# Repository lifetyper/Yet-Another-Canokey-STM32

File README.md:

# Yet-Another-Canokey-STM32
使用USBA Connector替代PCB金手指形式的焊盘，降低在加工厂打样的PCB成本。原理图和官方[Canokey-STM32](https://github.com/canokeys/canokey-stm32)版本一致。

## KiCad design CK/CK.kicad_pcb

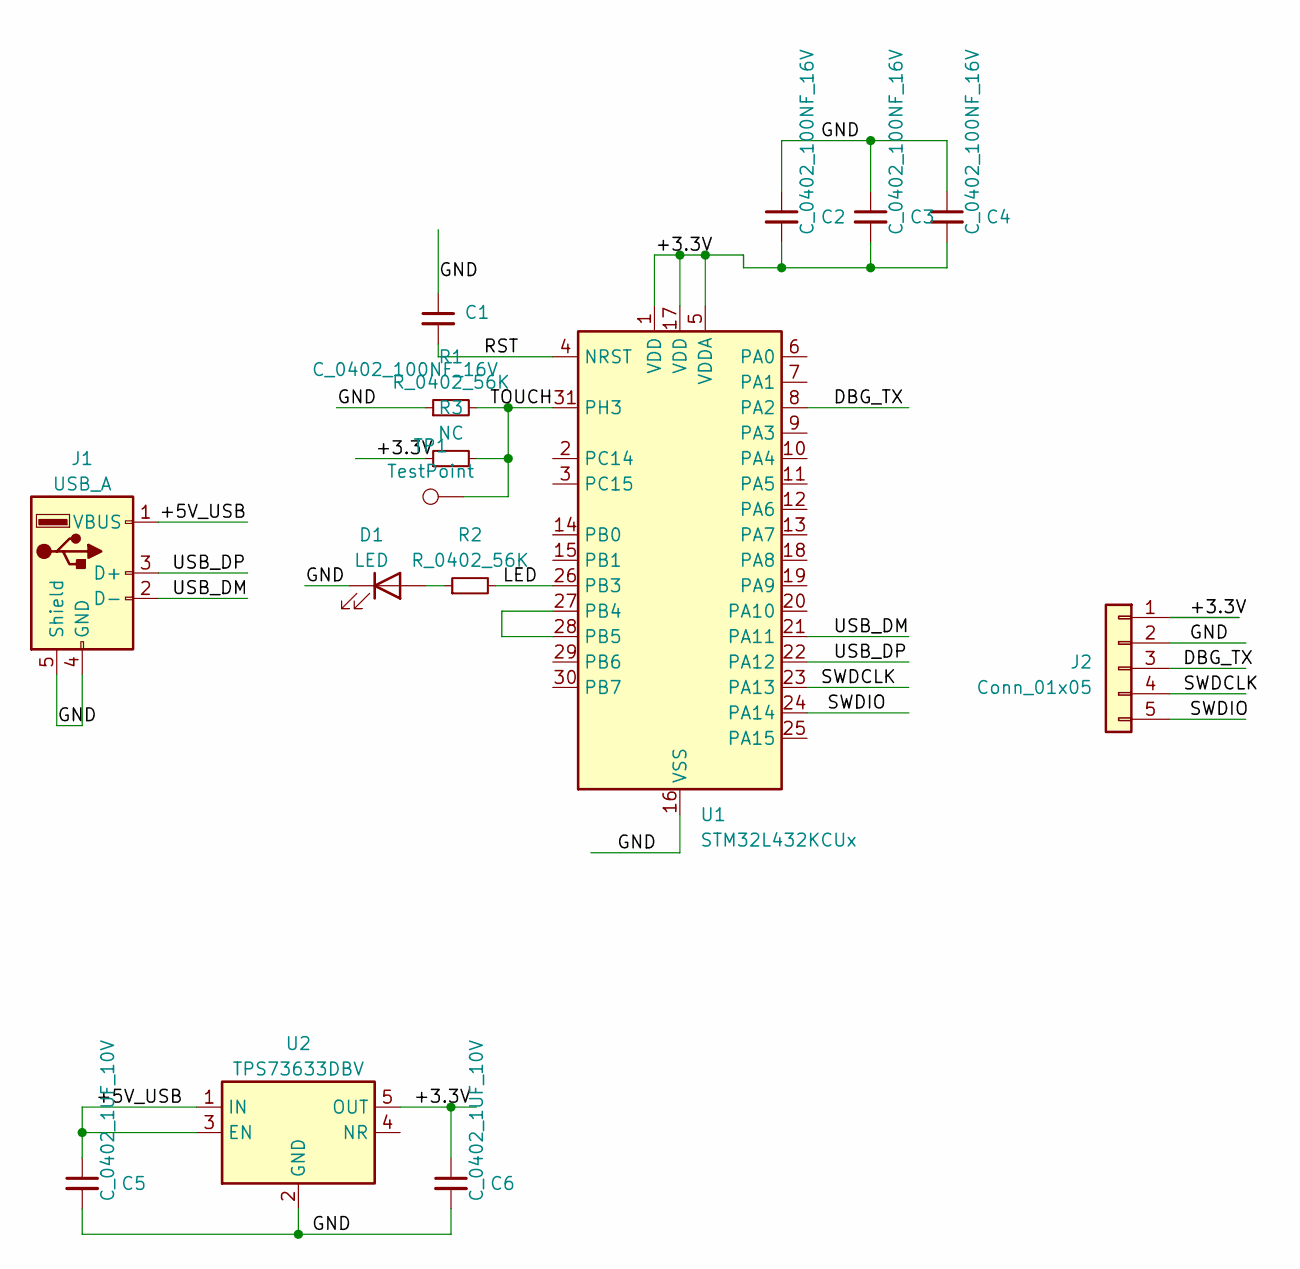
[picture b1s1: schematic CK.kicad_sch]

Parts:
C1, C2, C3, C4: C_0402_100NF_16V; C_0402_1005Metric
C5, C6: C_0402_1UF_10V; C_0402_1005Metric
D1: LED; LED_0603_1608Metric
J1: USB_A; USB_A_CNCTech_1001-011-01101_Horizontal
J2: Conn_01x05; PinHeader_1x05_P2.54mm_Vertical
R1, R2: R_0402_56K; R_0402_1005Metric
R3: NC; R_0402_1005Metric
TP1: TestPoint; CapSensor_8mm
U1: STM32L432KCUx; QFN-32-1EP_5x5mm_P0.5mm_EP3.45x3.45mm
U2: TPS73633DBV; SOT-23-5

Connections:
/+3.3V: C2.2, C3.2, C4.2, C6.1, J2.1, R3.1, U1.1 (VDD), U1.5 (VDDA), U1.17 (VDD), U2.5 (OUT)
/+5V_USB: C5.1, J1.1 (VBUS), U2.1 (IN), U2.3 (EN)
/DBG_TX: J2.3, U1.8 (PA2)
/GND: C1.1, C2.1, C3.1, C4.1, C5.2, C6.2, D1.1 (K), J1.4 (GND), J1.5 (Shield), J2.2, R1.1, U1.16 (VSS), U1.32 (VSS), U1.33 (VSS), U2.2 (GND)
/LED: R2.2, U1.26 (PB3)
/RST: C1.2, U1.4 (NRST)
/SWDCLK: J2.4, U1.23 (PA13)
/SWDIO: J2.5, U1.24 (PA14)
/TOUCH: R1.2, R3.2, TP1.1, U1.31 (PH3)
/USB_DM: J1.2 (D-), U1.21 (PA11)
/USB_DP: J1.3 (D+), U1.22 (PA12)
unnamed: D1.2 (A), R2.1
unnamed: U1.27 (PB4), U1.28 (PB5)

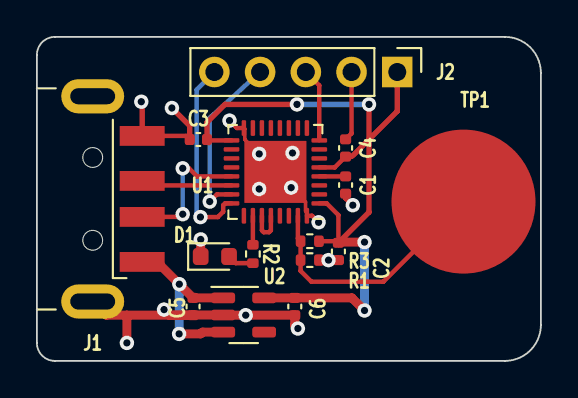
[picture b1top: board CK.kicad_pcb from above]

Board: 2 copper layers, 28.0 x 18.0 mm, 15 parts (0 on the bottom side), 13 nets.

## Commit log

2023-03-04 initial hardware
